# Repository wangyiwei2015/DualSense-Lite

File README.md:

# DualSense Lite

2022年，本科毕业设计

激光/超声 双模旋转扫描平台

本仓库为论文提供参考源代码。

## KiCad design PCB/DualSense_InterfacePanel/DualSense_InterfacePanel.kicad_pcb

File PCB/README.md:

# DualSense Lite - PCB

PCB 设计文件，KiCAD 工程。

- CH-x01 Driver - 为 TDK 的 PMUT IC 设计的驱动板，使用 IIC 与微处理器通信
- DualSense Lite 主板 - 集成了连接外设的逻辑电路与驱动电路
- DualSense Lite 接口板 - 开关、电源线、USB 数据线

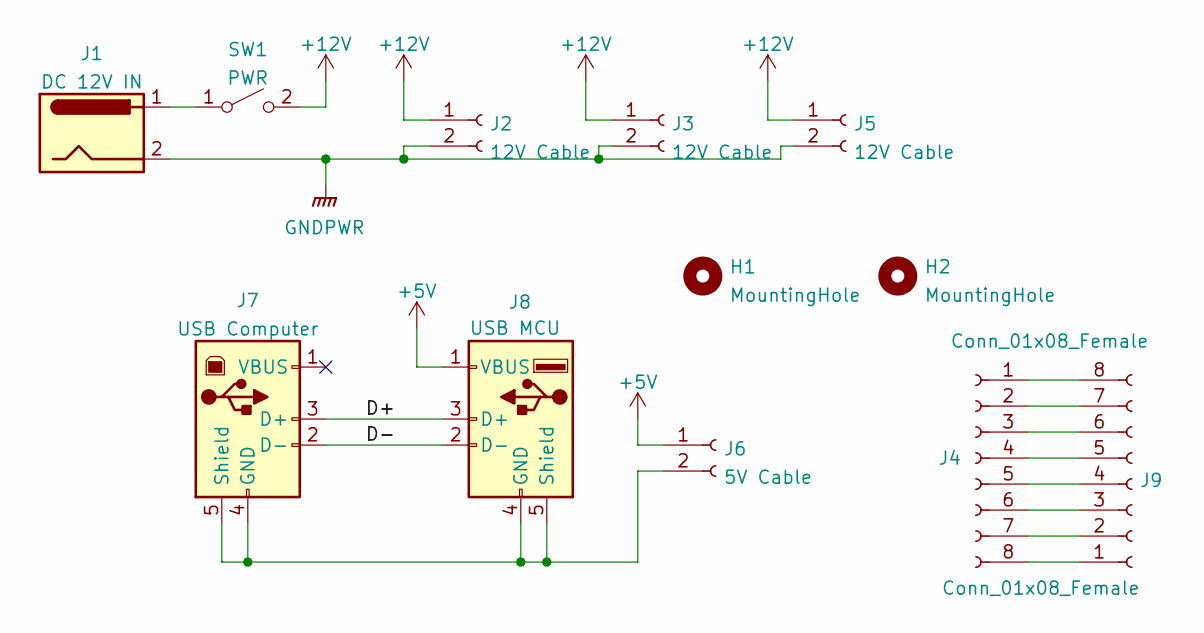
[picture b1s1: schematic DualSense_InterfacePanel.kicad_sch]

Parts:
H1, H2: MountingHole; MountingHole_3.2mm_M3_Pad_Via
J1: DC 12V IN; BarrelJack_SwitchcraftConxall_RAPC10U_Horizontal
J2, J3, J5: 12V Cable; Solder_Cables
J4, J9: Conn_01x08_Female; JST_XH_B8B-XH-A_1x08_P2.50mm_Vertical
J6: 5V Cable; Solder_Cables
J7: USB Computer; USB_B_Lumberg_2411_02_Horizontal
J8: USB MCU; USB_A_CONNFLY_DS1095-WNR0
SW1: PWR; Solder_Cables

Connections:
+5V: J6.1, J8.1 (VBUS)
+12V: J2.1, J3.1, J5.1, SW1.2 (B)
/D+: J7.3 (D+), J8.3 (D+)
/D-: J7.2 (D-), J8.2 (D-)
GNDPWR: J1.2, J2.2, J3.2, J5.2
unnamed: J1.1, SW1.1 (A)
unnamed: J4.1, J9.8
unnamed: J4.2, J9.7
unnamed: J4.3, J9.6
unnamed: J4.4, J9.5
unnamed: J4.5, J9.4
unnamed: J4.6, J9.3
unnamed: J4.7, J9.2
unnamed: J4.8, J9.1
unnamed: J6.2, J7.4 (GND), J7.5 (Shield), J8.4 (GND), J8.5 (Shield)

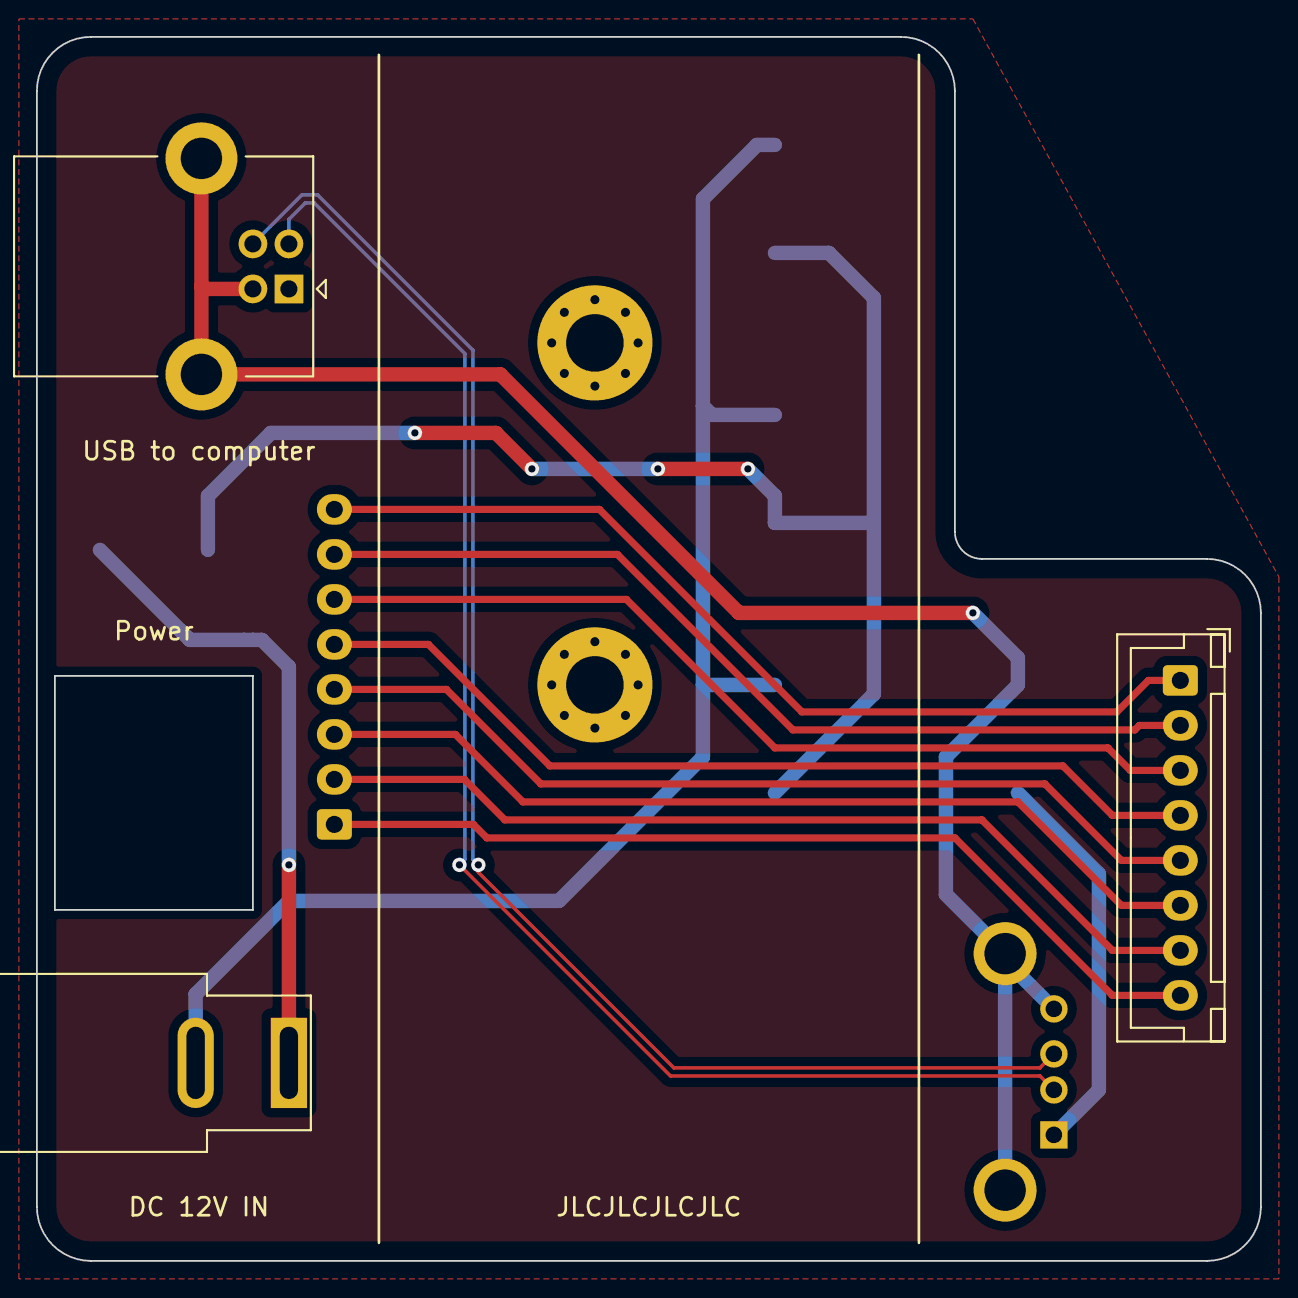
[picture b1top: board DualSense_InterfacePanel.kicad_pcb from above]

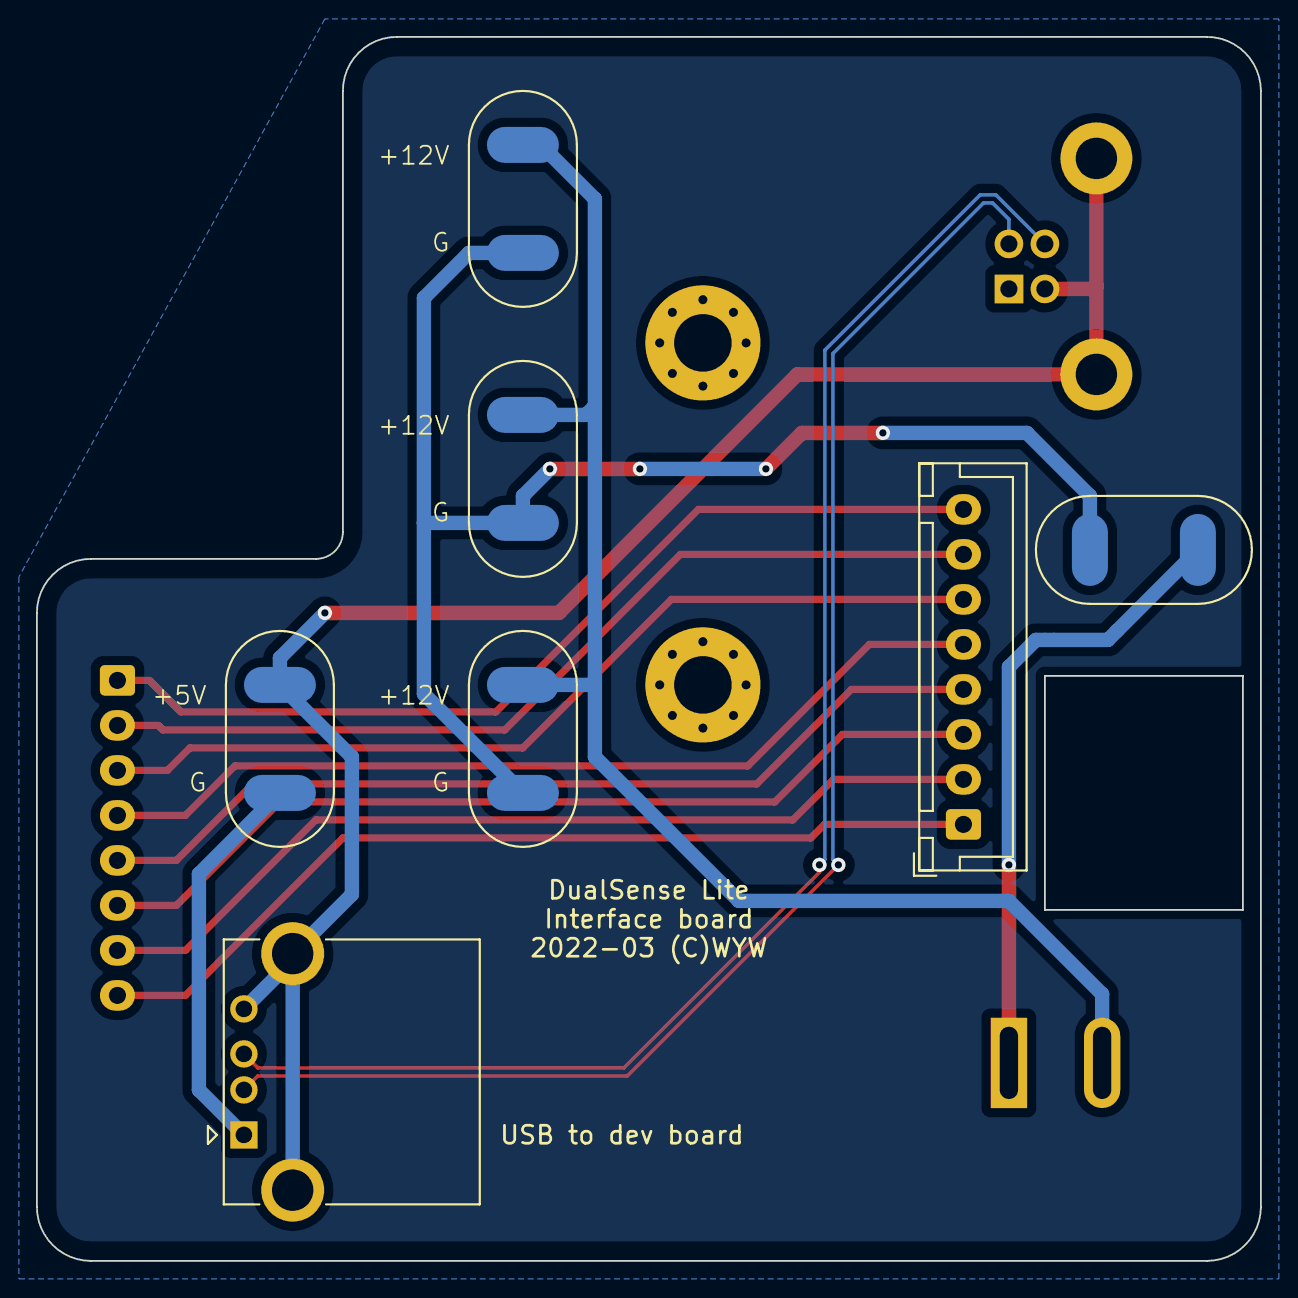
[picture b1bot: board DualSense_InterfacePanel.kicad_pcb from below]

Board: 2 copper layers, 68.0 x 68.0 mm, 12 parts (7 on the bottom side), 15 nets.

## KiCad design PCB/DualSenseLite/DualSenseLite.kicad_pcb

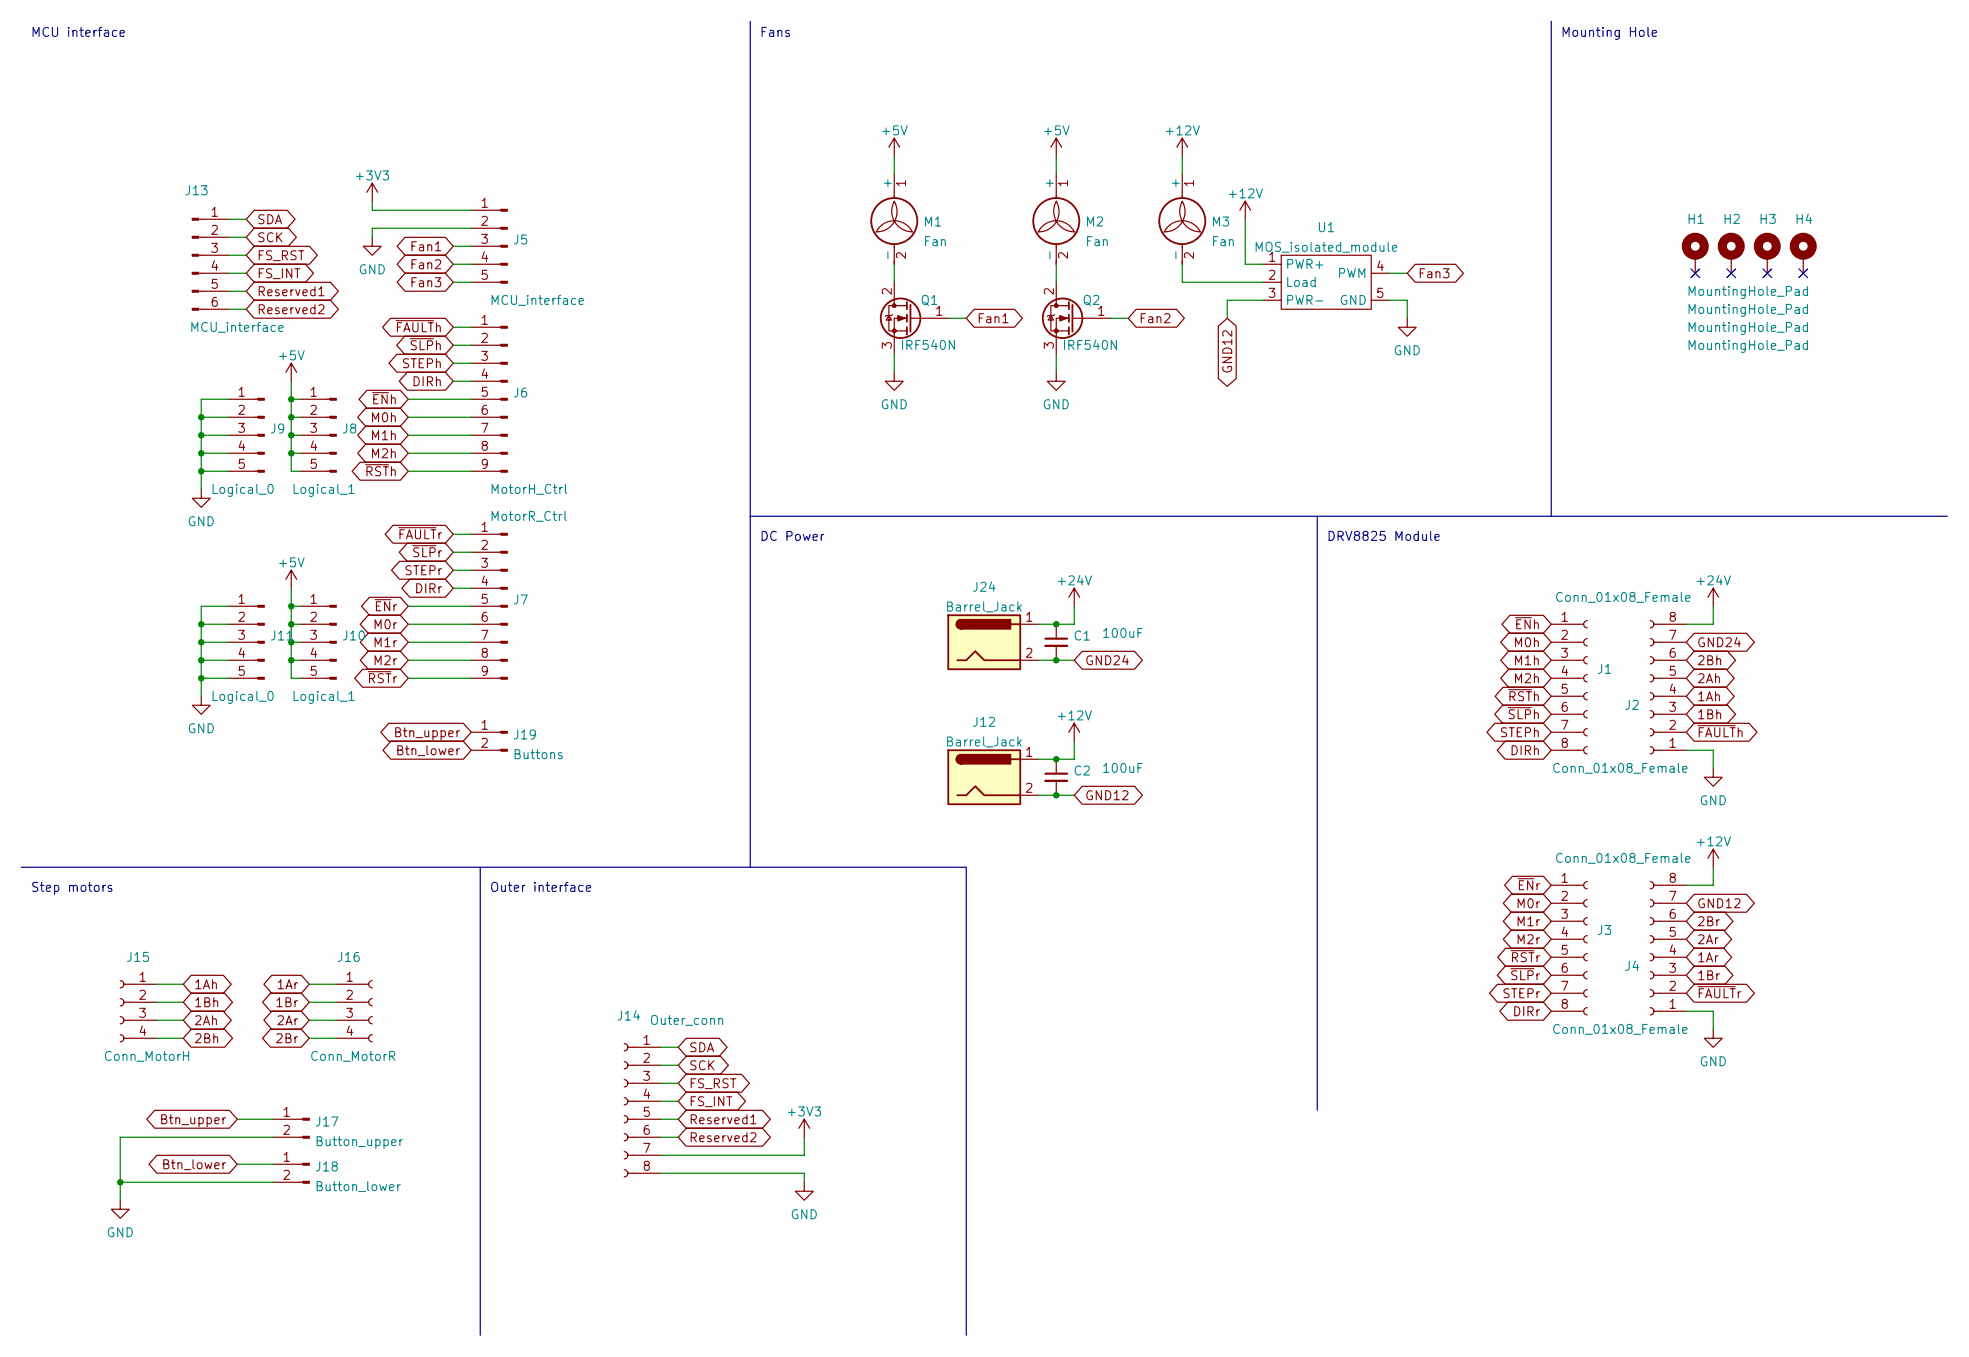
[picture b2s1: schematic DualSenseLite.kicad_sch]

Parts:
C1, C2: 100uF; C_0805_2012Metric_Pad1.18x1.45mm_HandSolder
H1, H2, H3, H4: MountingHole_Pad; MountingHole_3.2mm_M3_Pad_Via
J1, J2, J3, J4: Conn_01x08_Female; PinHeader_1x08_P2.54mm_Vertical
J5: MCU_interface; PinSocket_1x05_P2.54mm_Vertical
J6: MotorH_Ctrl; PinSocket_1x09_P2.54mm_Vertical
J7: MotorR_Ctrl; PinSocket_1x09_P2.54mm_Vertical
J8, J10: Logical_1; PinSocket_1x05_P2.54mm_Vertical
J9, J11: Logical_0; PinSocket_1x05_P2.54mm_Vertical
J12, J24: Barrel_Jack; BarrelJack_SwitchcraftConxall_RAPC10U_Horizontal
J13: MCU_interface; PinHeader_2x03_P2.54mm_Vertical
J14: Outer_conn; JST_XH_S8B-XH-A-1_1x08_P2.50mm_Horizontal
J15: Conn_MotorH; PinSocket_1x04_P2.54mm_Vertical
J16: Conn_MotorR; JST_PH_B4B-PH-K_1x04_P2.00mm_Vertical
J17: Button_upper; PinHeader_1x02_P2.54mm_Vertical
J18: Button_lower; PinHeader_1x02_P2.54mm_Vertical
J19: Buttons; PinSocket_1x02_P2.54mm_Vertical
M1, M2, M3: Fan; JST_XH_B2B-XH-A_1x02_P2.50mm_Vertical
Q1, Q2: IRF540N; TO-220-3_Vertical
U1: MOS_isolated_module; MOSFET_5pin

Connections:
1Ah: J2.4, J15.1
1Ar: J4.4, J16.1
1Bh: J2.3, J15.2
1Br: J4.3, J16.2
2Ah: J2.5, J15.3
2Ar: J4.5, J16.3
2Bh: J2.6, J15.4
2Br: J4.6, J16.4
+3V3: J5.1, J14.7
+5V: J8.1, J8.2, J8.3, J8.4, J8.5, J10.1, J10.2, J10.3, J10.4, J10.5, M1.1 (+), M2.1 (+)
+12V: C2.1, J4.8, J12.1, M3.1 (+), U1.1 (PWR+)
+24V: C1.1, J2.8, J24.1
Btn_lower: J18.1, J19.2
Btn_upper: J17.1, J19.1
DIRh: J1.8, J6.4
DIRr: J3.8, J7.4
FS_INT: J13.4, J14.4
FS_RST: J13.3, J14.3
Fan1: J5.3, Q1.1 (G)
Fan2: J5.4, Q2.1 (G)
Fan3: J5.5, U1.4 (PWM)
GND: J2.1, J4.1, J5.2, J9.1, J9.2, J9.3, J9.4, J9.5, J11.1, J11.2, J11.3, J11.4, J11.5, J14.8, J17.2, J18.2, Q1.3 (S), Q2.3 (S), U1.5 (GND)
GND12: C2.2, J4.7, J12.2, U1.3 (PWR-)
GND24: C1.2, J2.7, J24.2
M0h: J1.2, J6.6
M0r: J3.2, J7.6
M1h: J1.3, J6.7
M1r: J3.3, J7.7
M2h: J1.4, J6.8
M2r: J3.4, J7.8
unnamed: M1.2 (-), Q1.2 (D)
unnamed: M2.2 (-), Q2.2 (D)
unnamed: M3.2 (-), U1.2 (Load)
Reserved1: J13.5, J14.5
Reserved2: J13.6, J14.6
SCK: J13.2, J14.2
SDA: J13.1, J14.1
STEPh: J1.7, J6.3
STEPr: J3.7, J7.3
~ENh: J1.1, J6.5
~ENr: J3.1, J7.5
~FAULTh: J2.2, J6.1
~FAULTr: J4.2, J7.1
~RSTh: J1.5, J6.9
~RSTr: J3.5, J7.9
~SLPh: J1.6, J6.2
~SLPr: J3.6, J7.2

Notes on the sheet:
Outer interface
DC Power
Fans
Step motors
DRV8825 Module
Mounting Hole
MCU interface

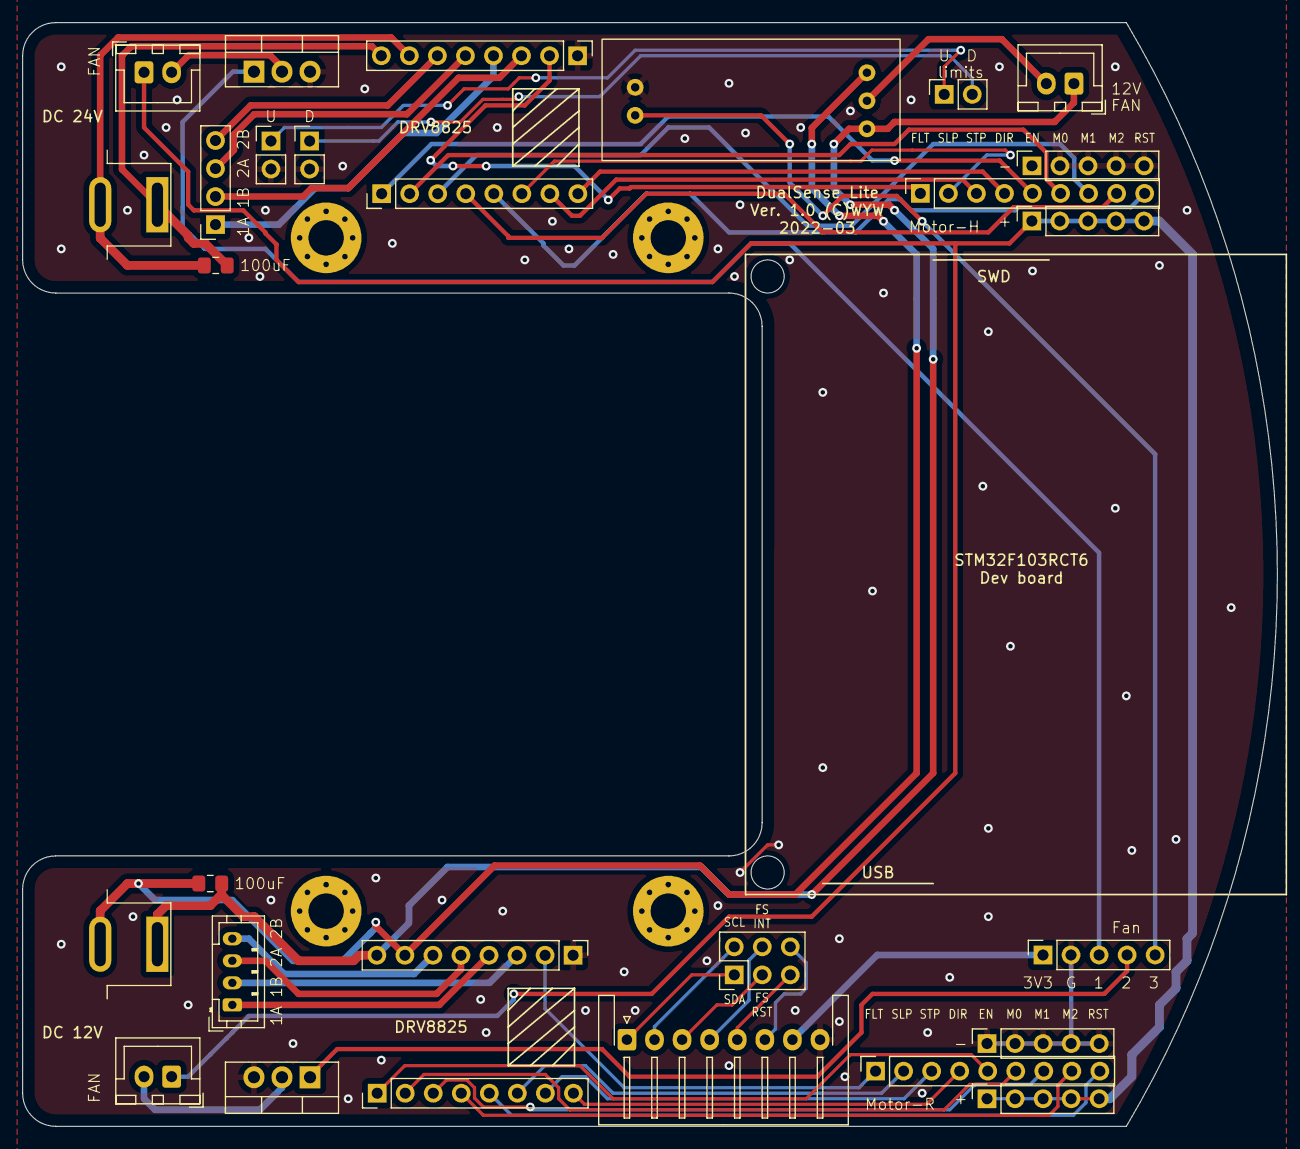
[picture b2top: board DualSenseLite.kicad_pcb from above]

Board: 2 copper layers, 113.7 x 100.0 mm, 32 parts (0 on the bottom side), 47 nets.

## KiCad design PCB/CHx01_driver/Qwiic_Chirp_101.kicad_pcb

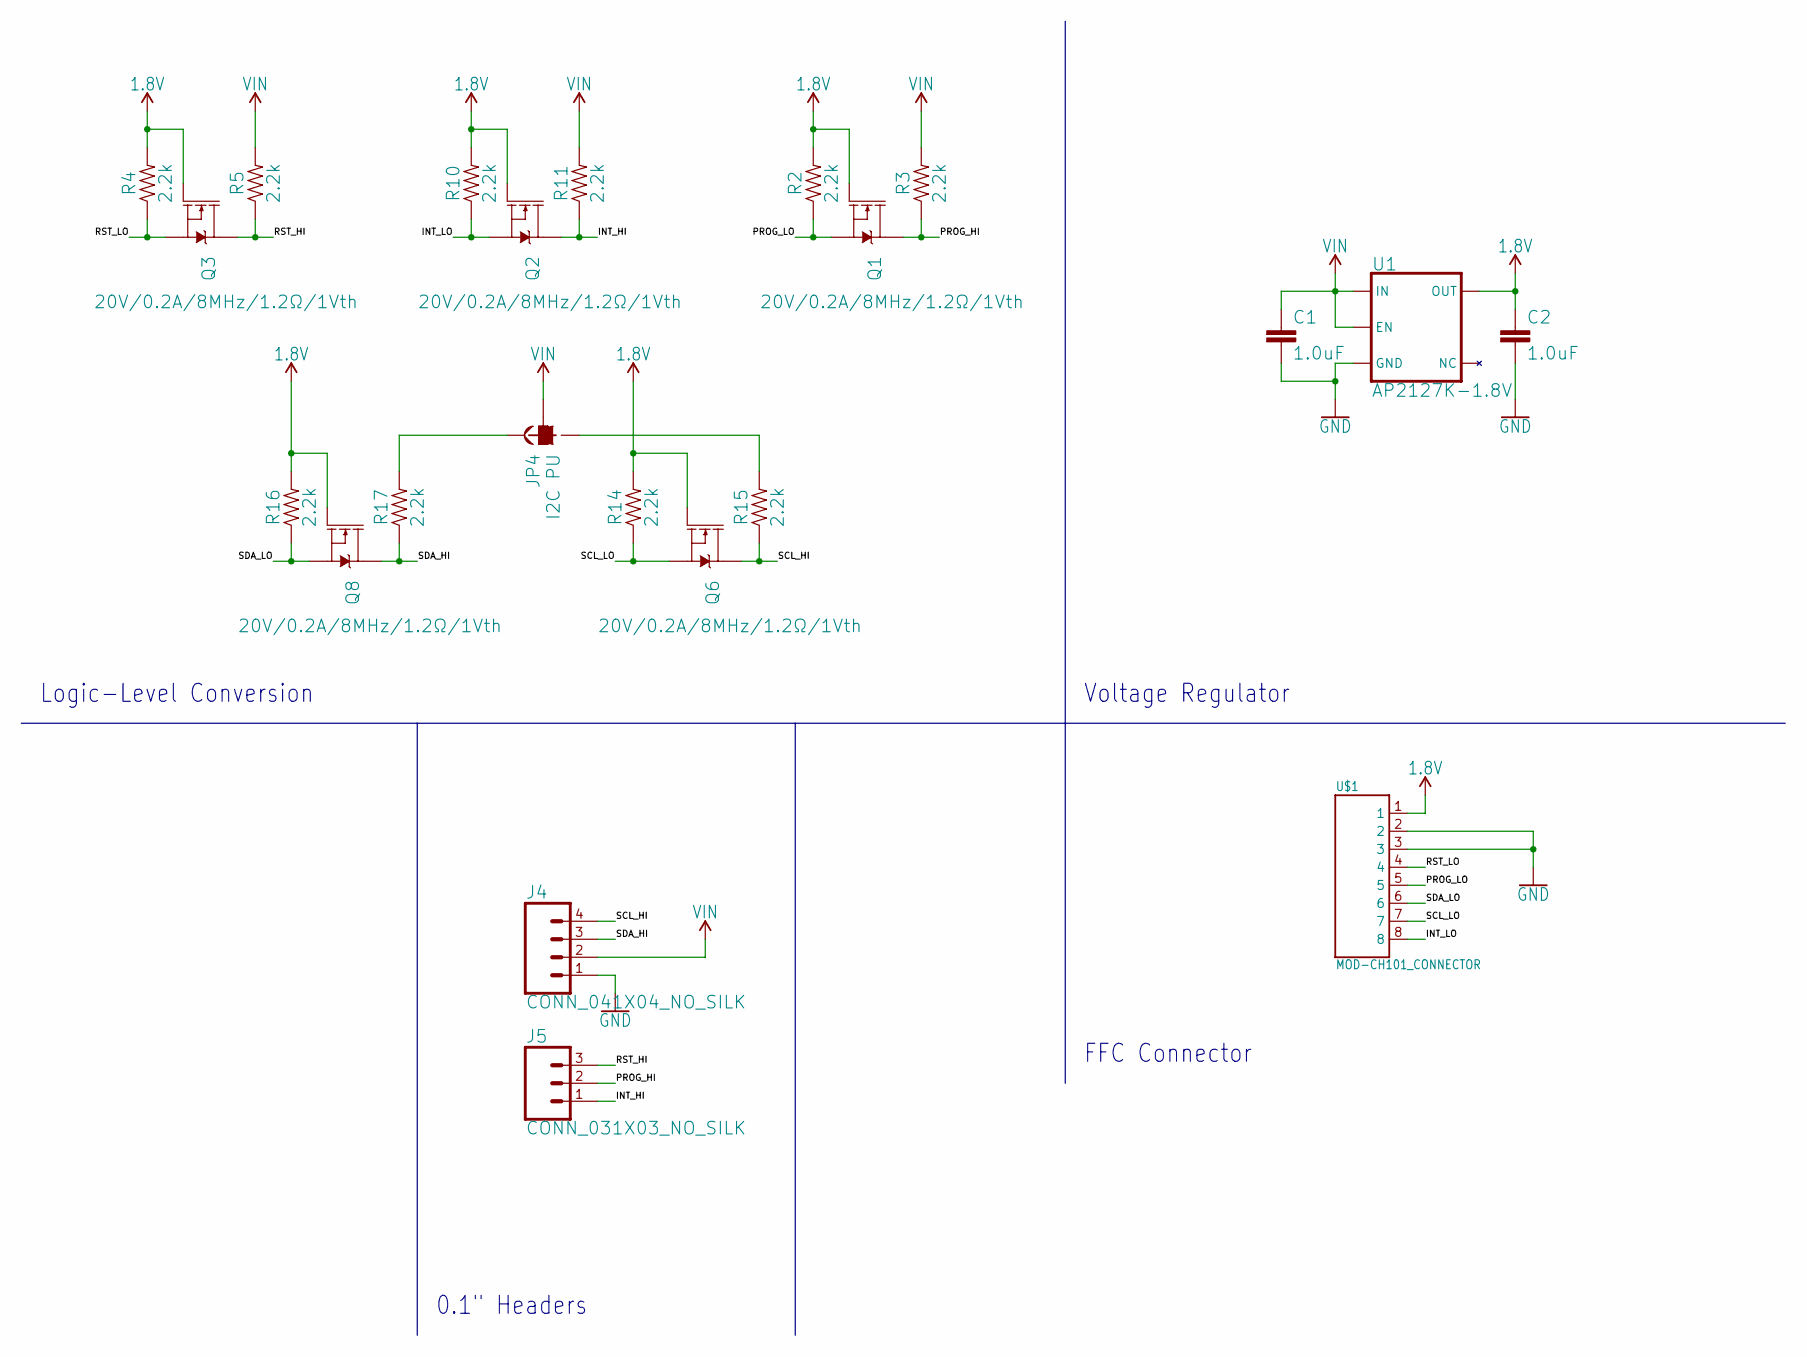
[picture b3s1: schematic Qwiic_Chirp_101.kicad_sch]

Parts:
C1, C2: 1.0uF; C_0805_2012Metric_Pad1.18x1.45mm_HandSolder
J4: CONN_041X04_NO_SILK; 1X04_NO_SILK
J5: CONN_031X03_NO_SILK; 1X03_NO_SILK
JP4: I2C PU; SMT-JUMPER_3_2-NC_TRACE_SILK
Q1, Q2, Q3, Q6, Q8: 20V/0.2A/8MHz/1.2Ω/1Vth; SOT-416FL
R2, R3, R4, R5, R10, R11, R14, R15, R16, R17: 2.2k; R_0805_2012Metric_Pad1.20x1.40mm_HandSolder
U1: AP2127K-1.8V; SOT23-5
U$1: MOD-CH101_CONNECTOR; FPC_MOLEX5034800800

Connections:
1.8V: C2.1, Q1.1 (G), Q2.1 (G), Q3.1 (G), Q6.1 (G), Q8.1 (G), R2.2, R4.2, R10.2, R14.2, R16.2, U1.5 (OUT), U$1.1; also elsewhere on the board
/INT_HI: J5.1, Q2.3 (D), R11.1
/INT_LO: Q2.2 (S), R10.1, U$1.8
/PROG_HI: J5.2, Q1.3 (D), R3.1
/PROG_LO: Q1.2 (S), R2.1, U$1.5
/RST_HI: J5.3, Q3.3 (D), R5.1
/RST_LO: Q3.2 (S), R4.1, U$1.4
/SCL_HI: J4.4, Q6.3 (D), R15.1
/SCL_LO: Q6.2 (S), R14.1, U$1.7
/SDA_HI: J4.3, Q8.3 (D), R17.1
/SDA_LO: Q8.2 (S), R16.1, U$1.6
GND: C1.2, C2.2, J4.1, U1.2 (GND), U$1.2, U$1.3; also elsewhere on the board
unnamed: JP4.1, R17.2
unnamed: JP4.3, R15.2
VIN: C1.1, J4.2, JP4.2, R3.2, R5.2, R11.2, U1.1 (IN), U1.3 (EN); also elsewhere on the board

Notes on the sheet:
FFC Connector
Logic-Level Conversion
Voltage Regulator
0.1" Headers

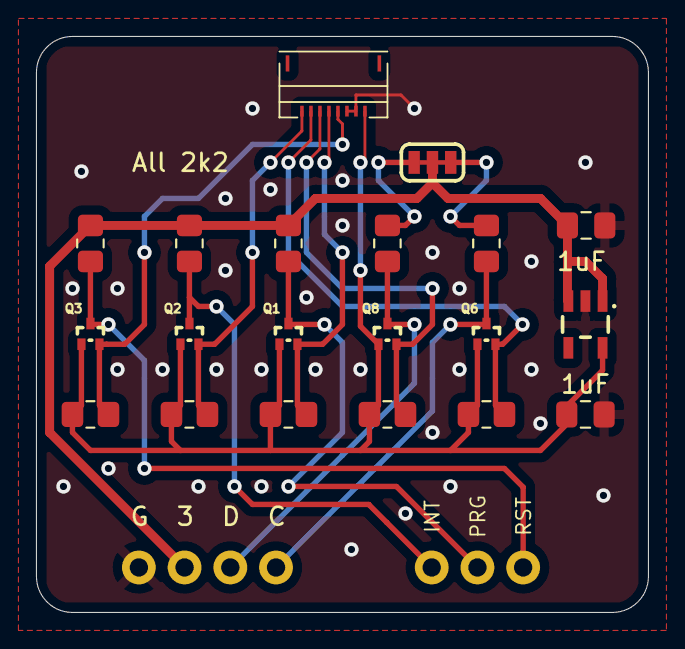
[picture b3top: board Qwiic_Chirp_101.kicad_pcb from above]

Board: 2 copper layers, 34.0 x 32.0 mm, 22 parts (0 on the bottom side), 15 nets.

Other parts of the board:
1uF, 1uF#2: 1.0uF; C_0805_2012Metric_Pad1.18x1.45mm_HandSolder

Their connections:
1.8V: 1uF#2.1; also elsewhere on the board
GND: 1uF.2, 1uF#2.2; also elsewhere on the board
VIN: 1uF.1; also elsewhere on the board

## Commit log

2022-05-19 init
2022-05-19 added designs and datasheets
2022-05-19 updated readmes
